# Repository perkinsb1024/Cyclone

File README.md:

# Cyclone

Don't forget to burn the fuses using the command in fuses.txt to get the timing set correctly

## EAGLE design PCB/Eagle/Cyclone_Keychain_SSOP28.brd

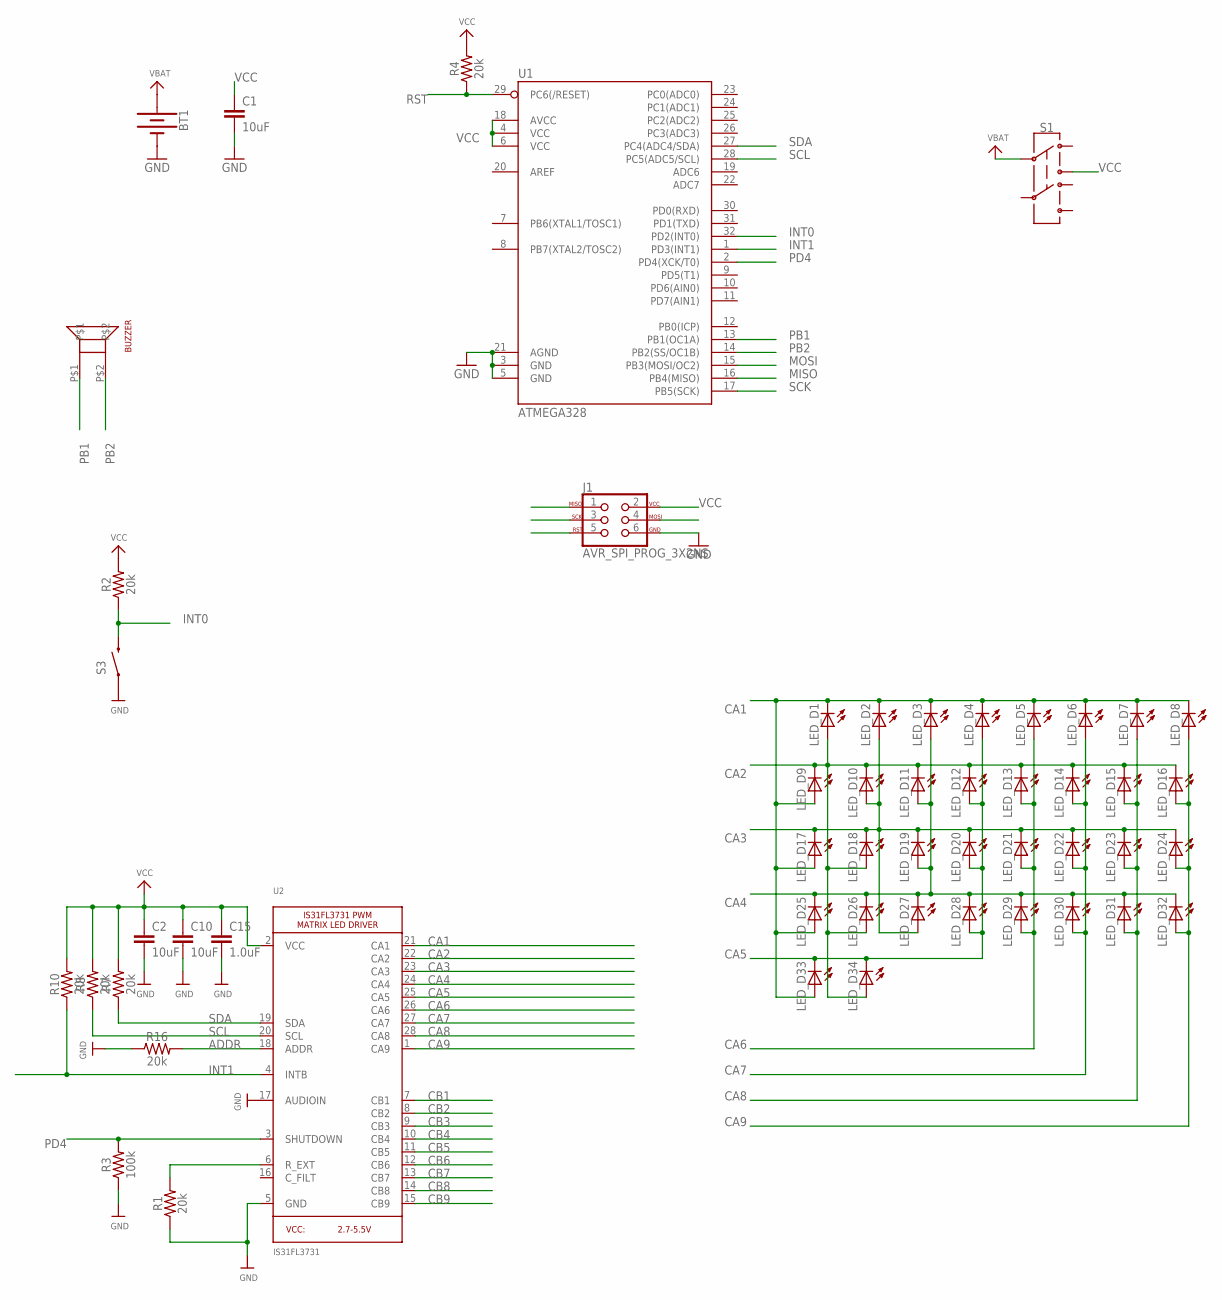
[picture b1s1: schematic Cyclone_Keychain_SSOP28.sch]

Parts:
BT1: BATTERY-20MM_PTH_WIDEPOS; BATTCOM_20MM_PTH_WIDEPOS
C1, C2, C10: 10uF; 0805
C15: 1.0uF; 0805
J1: AVR_SPI_PROG_3X2NS; 2X3-NS
LED_D1, LED_D2, LED_D3, LED_D4, LED_D5, LED_D6, LED_D7, LED_D8, LED_D9, LED_D10, LED_D11, LED_D12, LED_D13, LED_D14, LED_D15, LED_D16, LED_D17, LED_D18, LED_D19, LED_D20, LED_D21, LED_D22, LED_D23, LED_D24, LED_D25, LED_D26, LED_D27, LED_D28, LED_D29, LED_D30, LED_D31, LED_D32, LED_D33, LED_D34: LEDCHIP-LED0805; CHIP-LED0805
R1, R2, R4, R7, R8, R10, R16: 20k; 0805
R3: 100k; 0805
S1: SWITCH-DPDT-SMD-AYZ0202; SWITCH_DPDT_SMD_AYZ0202
S3: SWITCH-MOMENTARY-2SMD; TACTILE_SWITCH_SMD
U1: ATMEGA328; TQFP32-08
U2: IS31FL3731; SSOP28DB
U$11: PIEZO_BUZZER_SMT

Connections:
ADDR: R16.2, U2.18 (ADDR)
CA1: LED_D1.C, LED_D2.C, LED_D3.C, LED_D4.C, LED_D5.C, LED_D6.C, LED_D7.C, LED_D8.C, LED_D9.A, LED_D17.A, LED_D25.A, LED_D33.A, U2.21 (CA1)
CA2: LED_D1.A, LED_D9.C, LED_D10.C, LED_D11.C, LED_D12.C, LED_D13.C, LED_D14.C, LED_D15.C, LED_D16.C, LED_D18.A, LED_D26.A, LED_D34.A, U2.22 (CA2)
CA3: LED_D2.A, LED_D10.A, LED_D17.C, LED_D18.C, LED_D19.C, LED_D20.C, LED_D21.C, LED_D22.C, LED_D23.C, LED_D24.C, LED_D27.A, U2.23 (CA3)
CA4: LED_D3.A, LED_D11.A, LED_D19.A, LED_D25.C, LED_D26.C, LED_D27.C, LED_D28.C, LED_D29.C, LED_D30.C, LED_D31.C, LED_D32.C, U2.24 (CA4)
CA5: LED_D4.A, LED_D12.A, LED_D20.A, LED_D28.A, LED_D33.C, LED_D34.C, U2.25 (CA5)
CA6: LED_D5.A, LED_D13.A, LED_D21.A, LED_D29.A, U2.26 (CA6)
CA7: LED_D6.A, LED_D14.A, LED_D22.A, LED_D30.A, U2.27 (CA7)
CA8: LED_D7.A, LED_D15.A, LED_D23.A, LED_D31.A, U2.28 (CA8)
CA9: LED_D8.A, LED_D16.A, LED_D24.A, LED_D32.A, U2.1 (CA9)
CB1: U2.7 (CB1)
CB2: U2.8 (CB2)
CB3: U2.9 (CB3)
CB4: U2.10 (CB4)
CB5: U2.11 (CB5)
CB6: U2.12 (CB6)
CB7: U2.13 (CB7)
CB8: U2.14 (CB8)
CB9: U2.15 (CB9)
GND: BT1.2 (-), C1.2, C2.2, C10.2, C15.2, J1.6, R1.1, R3.1, R16.1, S3.1, U1.3 (GND), U1.5 (GND), U1.21 (AGND), U2.5 (GND), U2.17 (AUDIOIN)
INT0: R2.1, S3.3 (2), U1.32 (PD2(INT0))
INT1: R10.1, U1.1 (PD3(INT1)), U2.4 (INTB)
MISO: J1.1, U1.16 (PB4(MISO))
MOSI: J1.4, U1.15 (PB3(MOSI/OC2))
PB1: U1.13 (PB1(OC1A)), U$11.P$1
PB2: U1.14 (PB2(SS/OC1B)), U$11.P$2
PD4: R3.2, U1.2 (PD4(XCK/T0)), U2.3 (SHUTDOWN)
RST: J1.5, R4.1, U1.29 (PC6(/RESET))
R_EXT: R1.2, U2.6 (R_EXT)
SCK: J1.3, U1.17 (PB5(SCK))
SCL: R8.1, U1.28 (PC5(ADC5/SCL)), U2.20 (SCL)
SDA: R7.1, U1.27 (PC4(ADC4/SDA)), U2.19 (SDA)
VBAT: BT1.1 (+), S1.2
VCC: C1.1, C2.1, C10.1, C15.1, J1.2, R2.2, R4.2, R7.2, R8.2, R10.2, S1.3, U1.4 (VCC), U1.6 (VCC), U1.18 (AVCC), U2.2 (VCC)

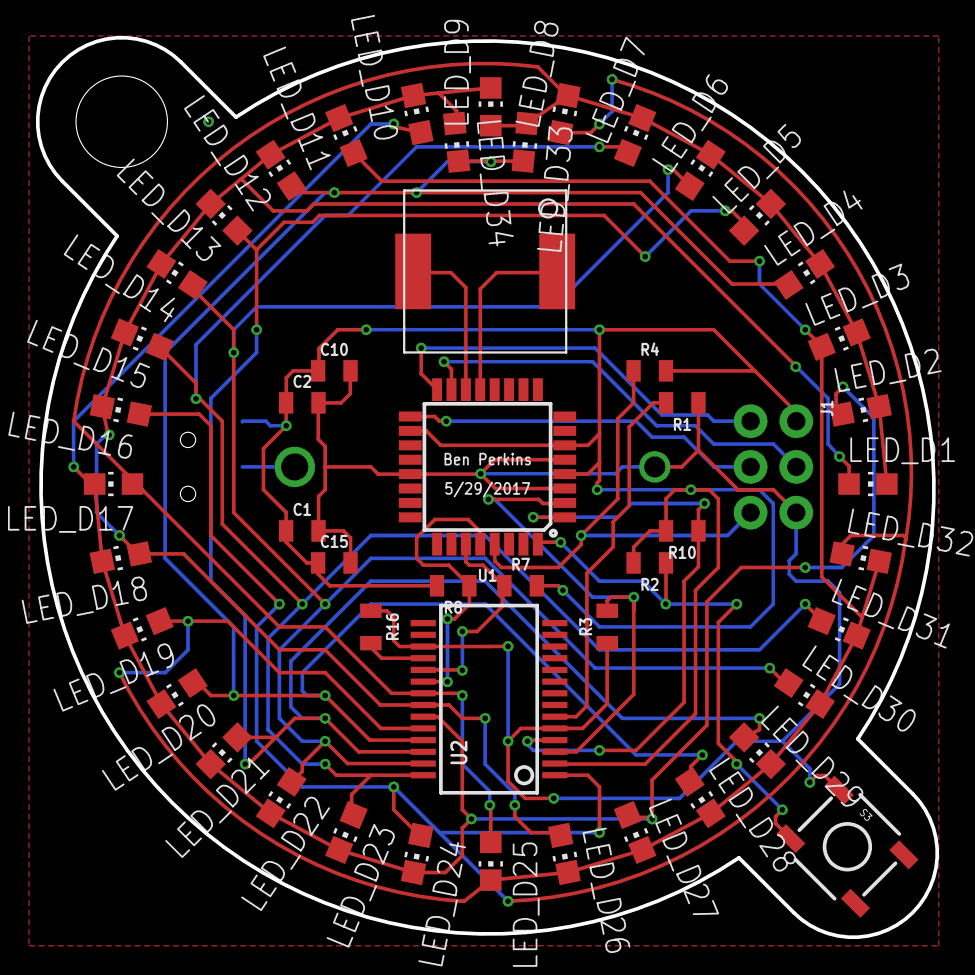
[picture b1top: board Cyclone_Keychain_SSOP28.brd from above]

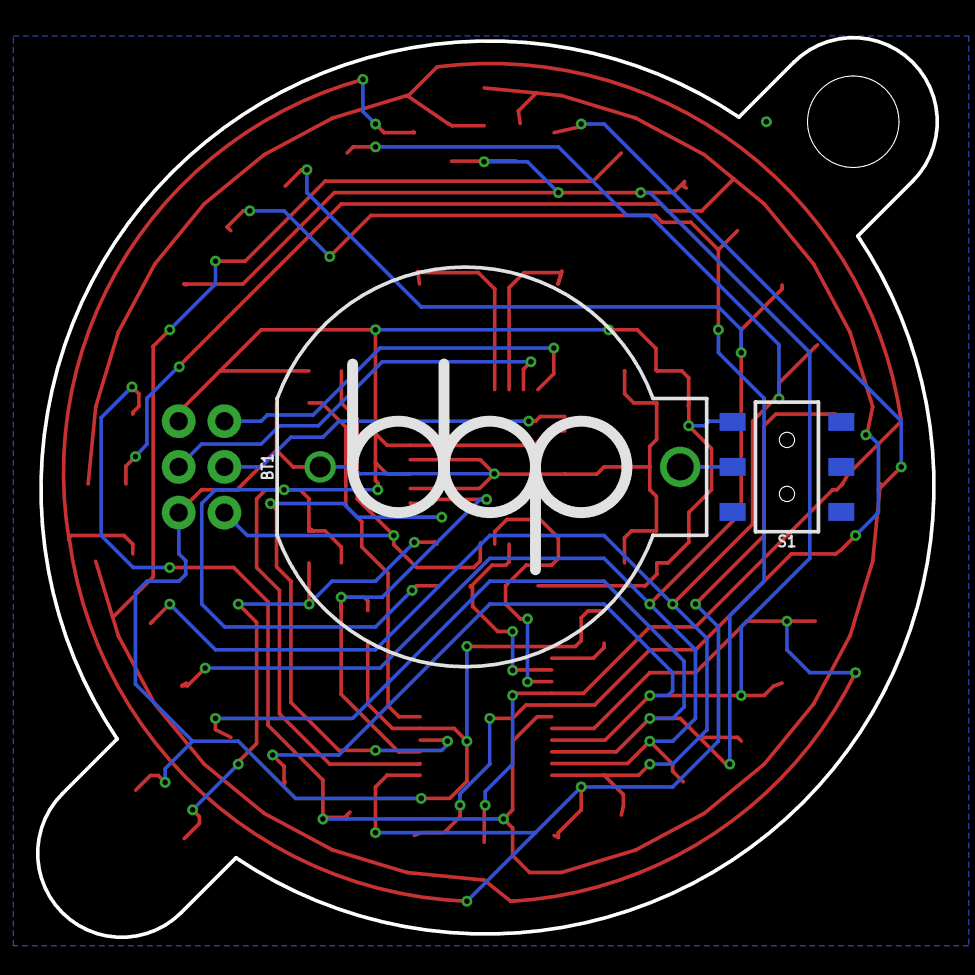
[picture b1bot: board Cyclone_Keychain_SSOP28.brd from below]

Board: 2 copper layers, 50.0 x 50.0 mm, 53 parts (2 on the bottom side), 25 nets.

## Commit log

2017-07-26 1.0 Arduino code, Eagle files and gerbers for Seeed Studios and OSHPark

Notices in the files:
parts and their libraries:
SparkFun-Connectors: Licensing: CC v3.0 Share-Alike You are welcome to use this library for commercial purposes.
SparkFun-IC-Microcontroller: Licensing: Creative Commons ShareAlike 4.0 International - https://creativecommons.org/licenses/by-sa/4.0
